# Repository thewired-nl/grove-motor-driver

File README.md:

# Grove-compatible Motor Driver TB6612

Circuit based on the [Adafruit breakout board](https://www.adafruit.com/product/2448) with the same chip, but with a Grove connector per motor channel and screw terminals for ease of use.
Datasheet: [TB6612FNG](https://cdn-shop.adafruit.com/datasheets/TB6612FNG_datasheet_en_20121101.pdf)

| Specs | |
| --- | --- |
| Motor voltage | 4.5 - 13.5v |
| Max amperage (per motor) | 1.2A (3.2A peak) |

This motor driver features 2 outputs (A and B), which can be individually controlled through their respective Grove connector.
Suitable for basic motors, linear actuators and solenoids.

# Wiring
Connect an external power supply between 4.5 - 13.v volts to the top screw terminal. Make sure ground is on the left (GND). Motor(s) can be connected to the outputs for Motor A (MA1, MA2) and/or Motor B (MB1, MB2) screw terminals. You can connect your motor wires either way, this only influences which throttle values will be forward/backward.

## Software
For use with CircuitPython, the [Adafruit motor library](https://docs.circuitpython.org/projects/motor/en/latest/index.html#) works quite well:

```python
import time
import board
import pwmio
import adafruit_motor

# One Grove port is used per motor output, make sure they don't have pin overlap
# TODO: figure out best PWM frequency

# A1, A2 Grove port connected to ItsyBitsy Expander port D2
pwmA1 = pwmio.PWMOut(board.D2, duty_cycle=0, frequency=5000)
pwmA2 = pwmio.PWMOut(board.D3, duty_cycle=0, frequency=5000)

# B1, B2 Grove port connected to ItsyBitsy Expander port D4
pwmB1 = pwmio.PWMOut(board.D4, duty_cycle=0, frequency=5000)
pwmB2 = pwmio.PWMOut(board.D7, duty_cycle=0, frequency=5000)

motorA = adafruit_motor.motor.DCMotor(pwmA1, pwmA2)
motorB = adafruit_motor.motor.DCMotor(pwmB1, pwmB2)

while True:
  # throttle ranges from -1.0 (full speed reverse) to 1.0 (full speed forward)
  motorA.throttle = 1
  motorB.throttle = 0
  time.sleep(2)
  motorA.throttle = -0.5
  motorB.throttle = -0.5
  time.sleep(2)
  motorA.throttle = 0
  motorB.throttle = 1
  time.sleep(2)
```

## License
[Creative Commons BY-SA 4.0](https://creativecommons.org/licenses/by-sa/4.0/)

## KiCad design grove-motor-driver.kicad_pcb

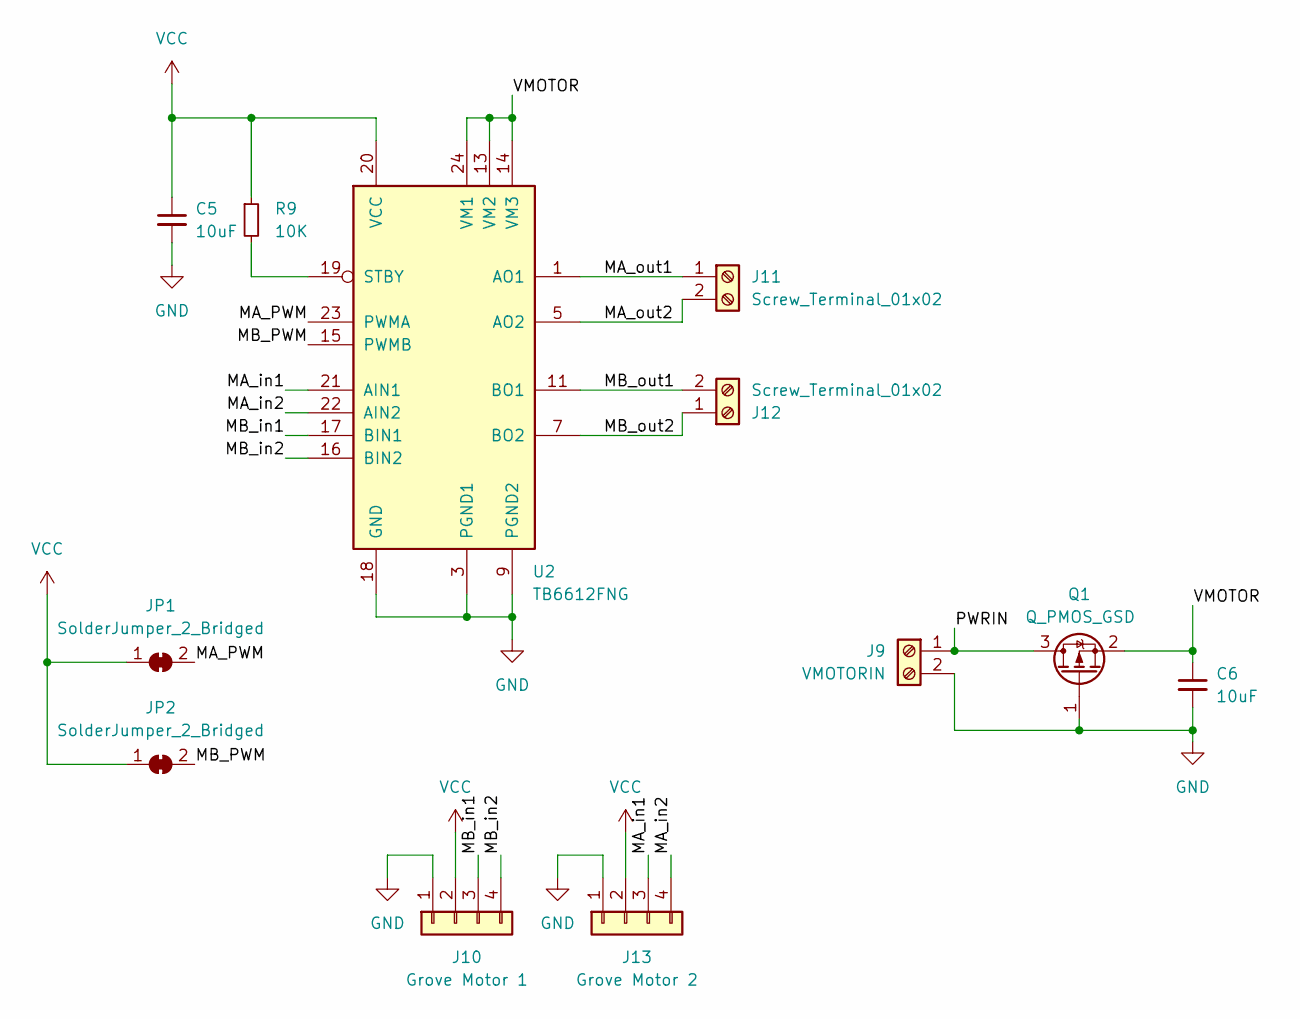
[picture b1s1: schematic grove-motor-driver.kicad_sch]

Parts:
C5, C6: 10uF; C_0805_2012Metric; MPN C15850
J9: VMOTORIN; DG301-5.0-2P-1X
J10: Grove Motor 1; GroveHorizontal
J11, J12: Screw_Terminal_01x02; DG301-5.0-2P-1X
J13: Grove Motor 2; GroveHorizontal
JP1, JP2: SolderJumper_2_Bridged; SolderJumper-2_P1.3mm_Bridged_Pad1.0x1.5mm
Q1: Q_PMOS_GSD; SOT-23; MPN C96616
R9: 10K; R_0402_1005Metric; MPN C25744
U2: TB6612FNG; SSOP-24_5.3x8.2mm_P0.65mm; MPN C88224

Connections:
/MA_PWM: JP1.2 (B), U2.23 (PWMA)
/MA_in1: J13.3, U2.21 (AIN1)
/MA_in2: J13.4, U2.22 (AIN2)
/MA_out1: J11.1, U2.1 (AO1), U2.2 (AO1)
/MA_out2: J11.2, U2.5 (AO2), U2.6 (AO2)
/MB_PWM: JP2.2 (B), U2.15 (PWMB)
/MB_in1: J10.3, U2.17 (BIN1)
/MB_in2: J10.4, U2.16 (BIN2)
/MB_out1: J12.2, U2.11 (BO1), U2.12 (BO1)
/MB_out2: J12.1, U2.7 (BO2), U2.8 (BO2)
/PWRIN: J9.1, Q1.3 (D)
/VMOTOR: C6.1, Q1.2 (S), U2.13 (VM2), U2.14 (VM3), U2.24 (VM1)
GND: C5.2, C6.2, J9.2, J10.1, J13.1, Q1.1 (G), U2.3 (PGND1), U2.4 (PGND1), U2.9 (PGND2), U2.10 (PGND2), U2.18 (GND)
unnamed: R9.2, U2.19 (STBY)
VCC: C5.1, J10.2, J13.2, JP1.1 (A), JP2.1 (A), R9.1, U2.20 (VCC)

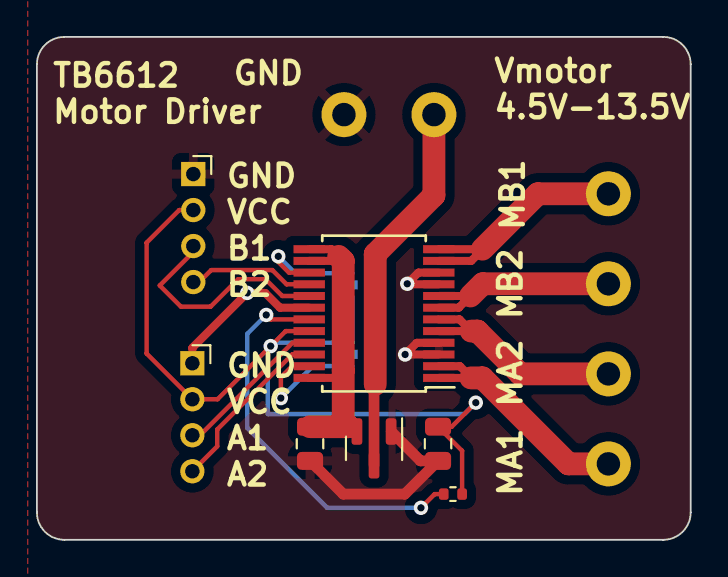
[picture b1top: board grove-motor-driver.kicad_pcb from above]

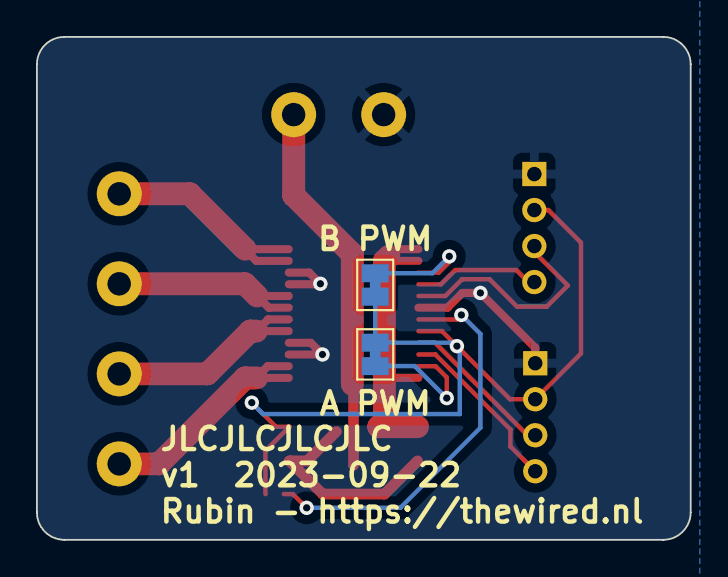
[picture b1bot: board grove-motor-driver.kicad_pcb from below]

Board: 2 copper layers, 36.3 x 27.9 mm, 12 parts (2 on the bottom side), 15 nets.

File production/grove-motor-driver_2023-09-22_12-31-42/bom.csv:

Designator,Footprint,Quantity,Value,LCSC Part #
"C5, C6",0805,2,10uF,C15850
J10,PinHeader_1x04_P2.00mm_Horizontal,1,Grove Motor 1,
"J11, J12",DG301-5.0-2P-1X,2,Screw_Terminal_01x02,
J13,PinHeader_1x04_P2.00mm_Horizontal,1,Grove Motor 2,
J9,DG301-5.0-2P-1X,1,VMOTORIN,
"JP1, JP2",SolderJumper-2_P1.3mm_Bridged_Pad1.0x1.5mm,2,SolderJumper_2_Bridged,
Q1,SOT-23,1,Q_PMOS_GSD,C96616
R9,0402,1,10K,C25744
U2,SSOP-24_5.3x8.2mm_P0.65mm,1,TB6612FNG,C88224

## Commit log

2023-11-06 release v1
